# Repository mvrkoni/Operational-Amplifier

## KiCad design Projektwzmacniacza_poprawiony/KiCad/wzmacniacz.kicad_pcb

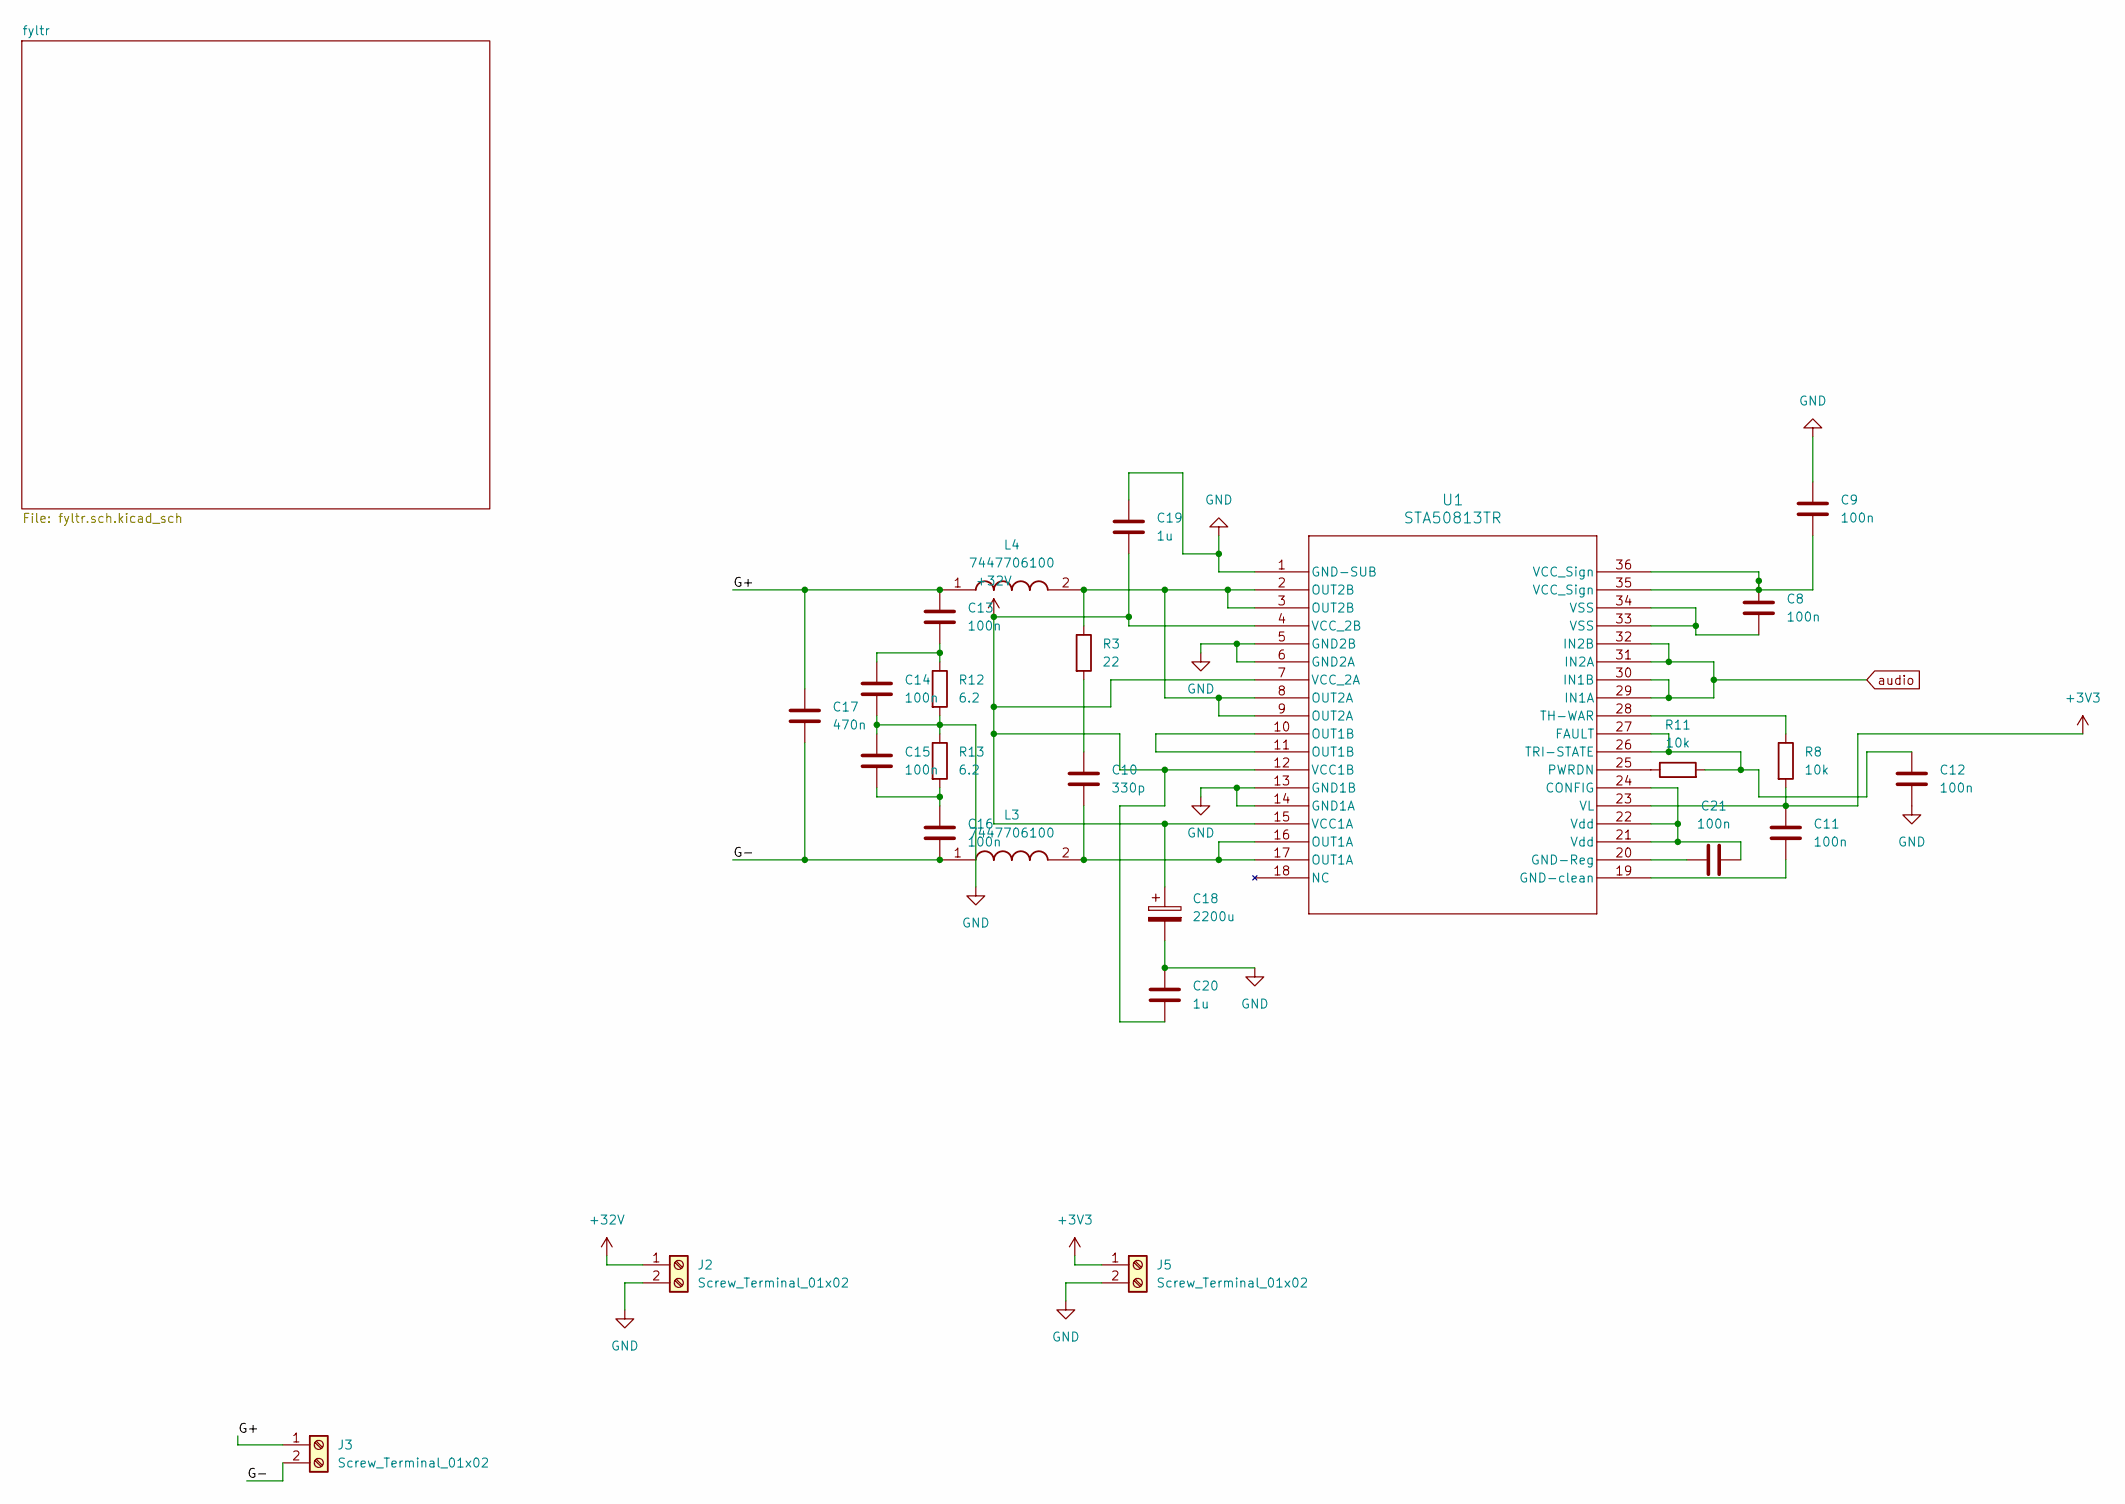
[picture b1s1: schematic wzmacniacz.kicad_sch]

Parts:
C8, C9, C11, C12, C13, C14, C15, C16, C21: 100n; C_0805_2012Metric
C10: 330p; C_0805_2012Metric
C17: 470n; C_0805_2012Metric
C18: 2200u; C_Radial_D18.0mm_H35.5mm_P7.50mm
C19, C20: 1u; C_0805_2012Metric
J2, J3, J5: Screw_Terminal_01x02; TerminalBlock_Phoenix_MPT-0,5-2-2.54_1x02_P2.54mm_Horizontal
L3, L4: 7447706100; Mouser Part Number 710-7447706100
R3: 22; R_0805_2012Metric
R8, R11: 10k; R_0805_2012Metric
R12, R13: 6.2; R_0805_2012Metric
U1: STA50813TR; SO_50813TR_STM

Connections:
+3V3: C11.1, J5.1, R8.2, U1.23 (VL)
+32V: C18.1, C19.2, C20.2, J2.1, U1.4 (VCC_2B), U1.7 (VCC_2A), U1.12 (VCC1B), U1.15 (VCC1A)
/G+: C13.1, C17.1, J3.1, L4.1
/G-: C16.2, C17.2, J3.2, L3.1
GND: C9.1, C12.2, C14.2, C15.1, C18.2, C19.1, C20.1, J2.2, J5.2, R12.2, R13.1, U1.1 (GND-SUB), U1.5 (GND2B), U1.6 (GND2A), U1.13 (GND1B), U1.14 (GND1A); also elsewhere on the board
unnamed: C8.1, C9.2, U1.35 (VCC_Sign), U1.36 (VCC_Sign)
unnamed: C8.2, U1.33 (VSS), U1.34 (VSS)
unnamed: C10.1, R3.2
unnamed: C10.2, L3.2, U1.16 (OUT1A), U1.17 (OUT1A)
unnamed: C13.2, C14.1, R12.1
unnamed: C15.2, C16.1, R13.2
unnamed: L4.2, R3.1, U1.2 (OUT2B), U1.3 (OUT2B), U1.8 (OUT2A), U1.9 (OUT2A)
unnamed: C21.2, U1.21 (Vdd), U1.22 (Vdd), U1.24 (CONFIG)
unnamed: C12.1, R11.2, U1.26 (TRI-STATE), U1.27 (FAULT)
unnamed: C21.1, U1.20 (GND-Reg)
unnamed: C11.2, U1.19 (GND-clean)
unnamed: U1.10 (OUT1B), U1.11 (OUT1B)
unnamed: R11.1, U1.25 (PWRDN)
unnamed: R8.1, U1.28 (TH-WAR)
audio: U1.29 (IN1A), U1.30 (IN1B), U1.31 (IN2A), U1.32 (IN2B); also elsewhere on the board

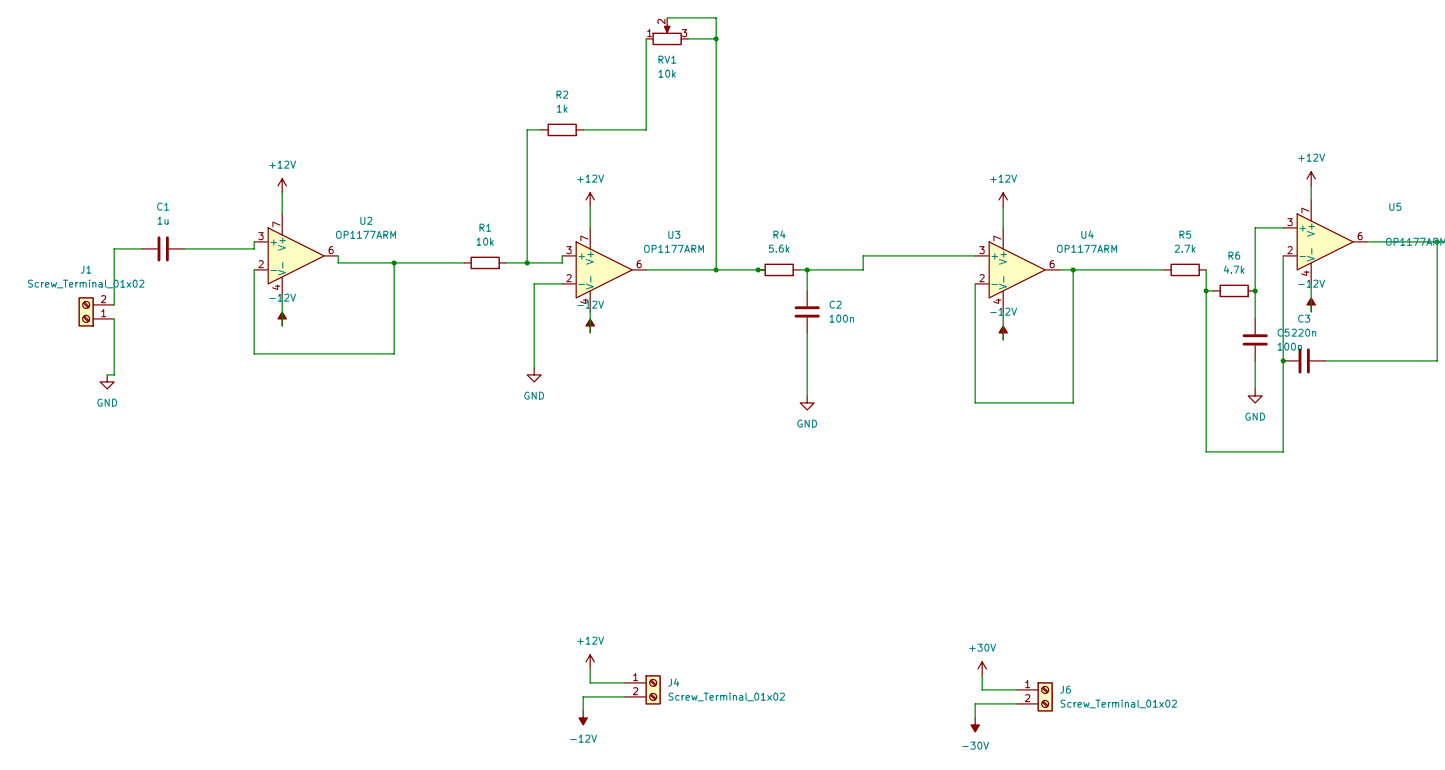
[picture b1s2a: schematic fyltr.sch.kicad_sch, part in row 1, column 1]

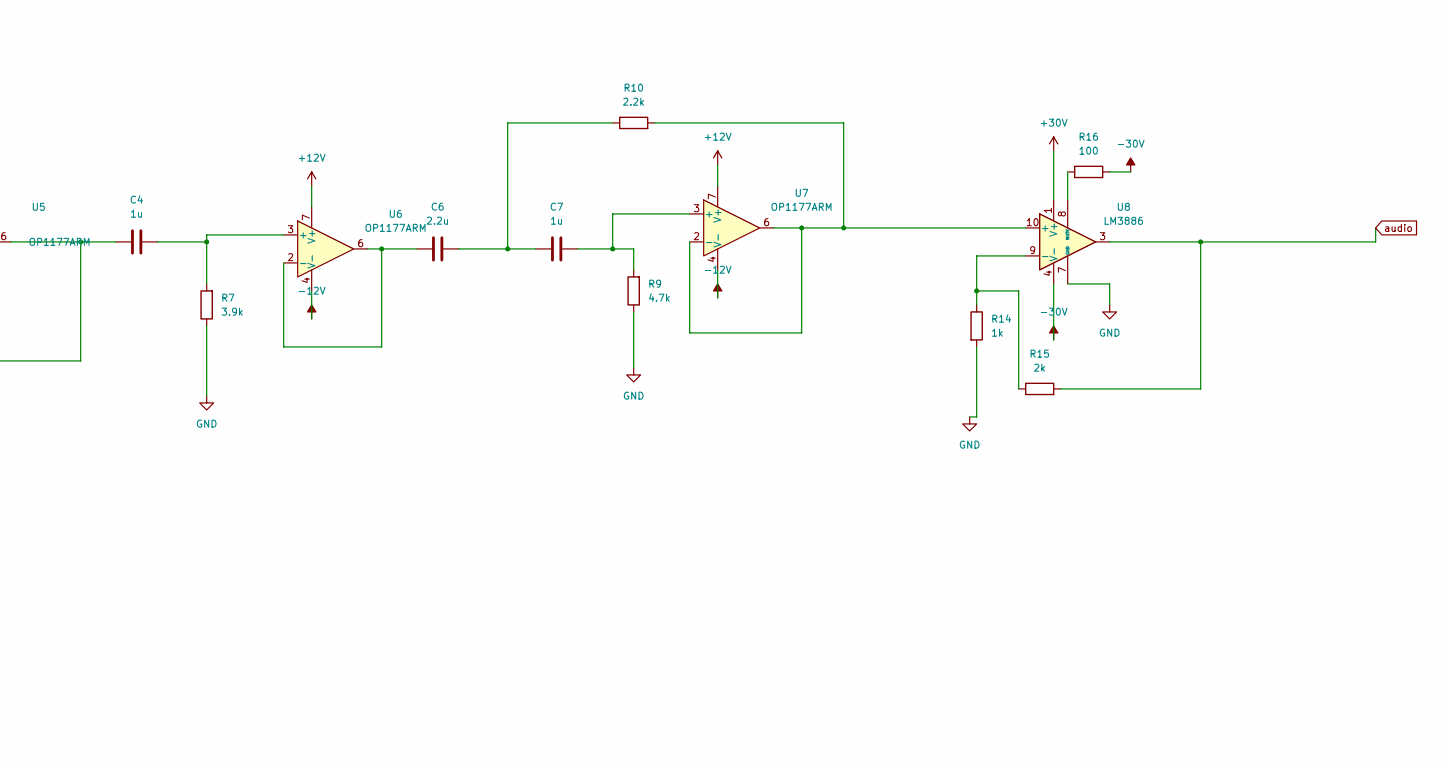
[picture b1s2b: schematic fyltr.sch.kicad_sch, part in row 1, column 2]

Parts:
C1, C4, C7: 1u; C_0805_2012Metric
C2, C5: 100n; C_0805_2012Metric
C3: 220n; C_0805_2012Metric
C6: 2.2u; C_0805_2012Metric
J1, J4, J6: Screw_Terminal_01x02; TerminalBlock_Phoenix_MPT-0,5-2-2.54_1x02_P2.54mm_Horizontal
R1: 10k; R_0805_2012Metric
R2, R14: 1k; R_0805_2012Metric
R4: 5.6k; R_0805_2012Metric
R5: 2.7k; R_0805_2012Metric
R6, R9: 4.7k; R_0805_2012Metric
R7: 3.9k; R_0805_2012Metric
R10: 2.2k; R_0805_2012Metric
R15: 2k; R_0805_2012Metric
R16: 100; R_0805_2012Metric
RV1: 10k; Potentiometer_Bourns_3214G_Horizontal
U2, U3, U4, U5, U6, U7: OP1177ARM; MSOP-8_3x3mm_P0.65mm
U8: LM3886; TO-220-11_P3.4x5.08mm_StaggerOdd_Lead4.85mm_Vertical

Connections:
+12V: J4.1, U2.7 (V+), U3.7 (V+), U4.7 (V+), U5.7 (V+), U6.7 (V+), U7.7 (V+)
+30V: J6.1, U8.1 (V+), U8.5 (V+)
-12V: J4.2, U2.4 (V-), U3.4 (V-), U4.4 (V-), U5.4 (V-), U6.4 (V-), U7.4 (V-)
-30V: J6.2, R16.2, U8.4 (V-)
GND: C2.1, C5.1, J1.1, R7.1, R9.1, R14.2, U3.2 (-), U8.7 (GND); also elsewhere on the board
unnamed: C3.2, C4.1, U5.6
unnamed: C6.2, C7.1, R10.1
unnamed: C1.1, J1.2
unnamed: R2.2, RV1.1
unnamed: R4.1, RV1.2, RV1.3, U3.6
unnamed: C1.2, U2.3 (+)
unnamed: R1.1, U2.2 (-), U2.6
unnamed: R1.2, R2.1, U3.3 (+)
unnamed: C2.2, R4.2, U4.3 (+)
unnamed: R5.1, U4.2 (-), U4.6
unnamed: C5.2, R6.2, U5.3 (+)
unnamed: C3.1, R5.2, R6.1, U5.2 (-)
unnamed: C4.2, R7.2, U6.3 (+)
unnamed: C6.1, U6.2 (-), U6.6
unnamed: C7.2, R9.2, U7.3 (+)
unnamed: R10.2, U7.2 (-), U7.6, U8.10 (+)
unnamed: R14.1, R15.1, U8.9 (-)
unnamed: R16.1, U8.8 (MUTE)
audio: R15.2, U8.3; also elsewhere on the board

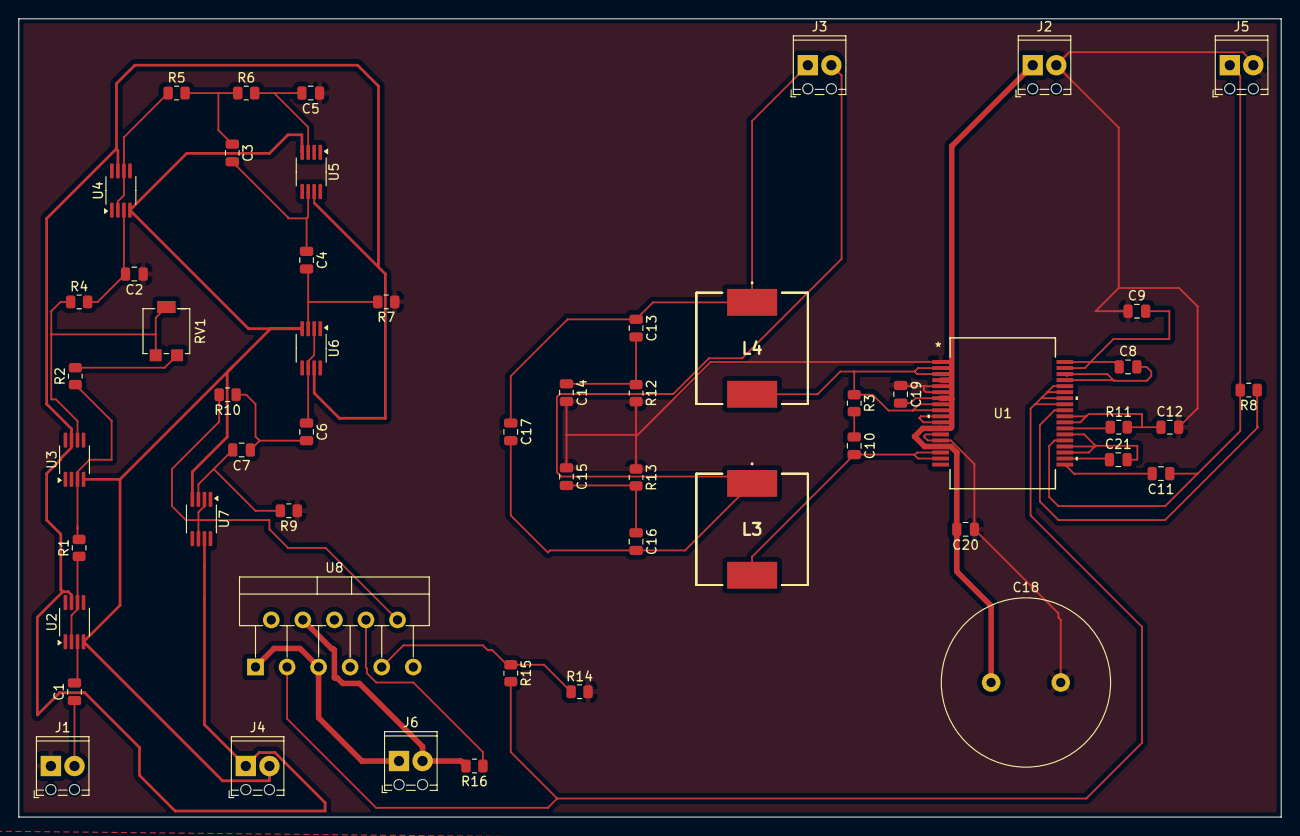
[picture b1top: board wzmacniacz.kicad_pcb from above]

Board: 2 copper layers, 136.0 x 86.0 mm, 54 parts (0 on the bottom side), 42 nets.
